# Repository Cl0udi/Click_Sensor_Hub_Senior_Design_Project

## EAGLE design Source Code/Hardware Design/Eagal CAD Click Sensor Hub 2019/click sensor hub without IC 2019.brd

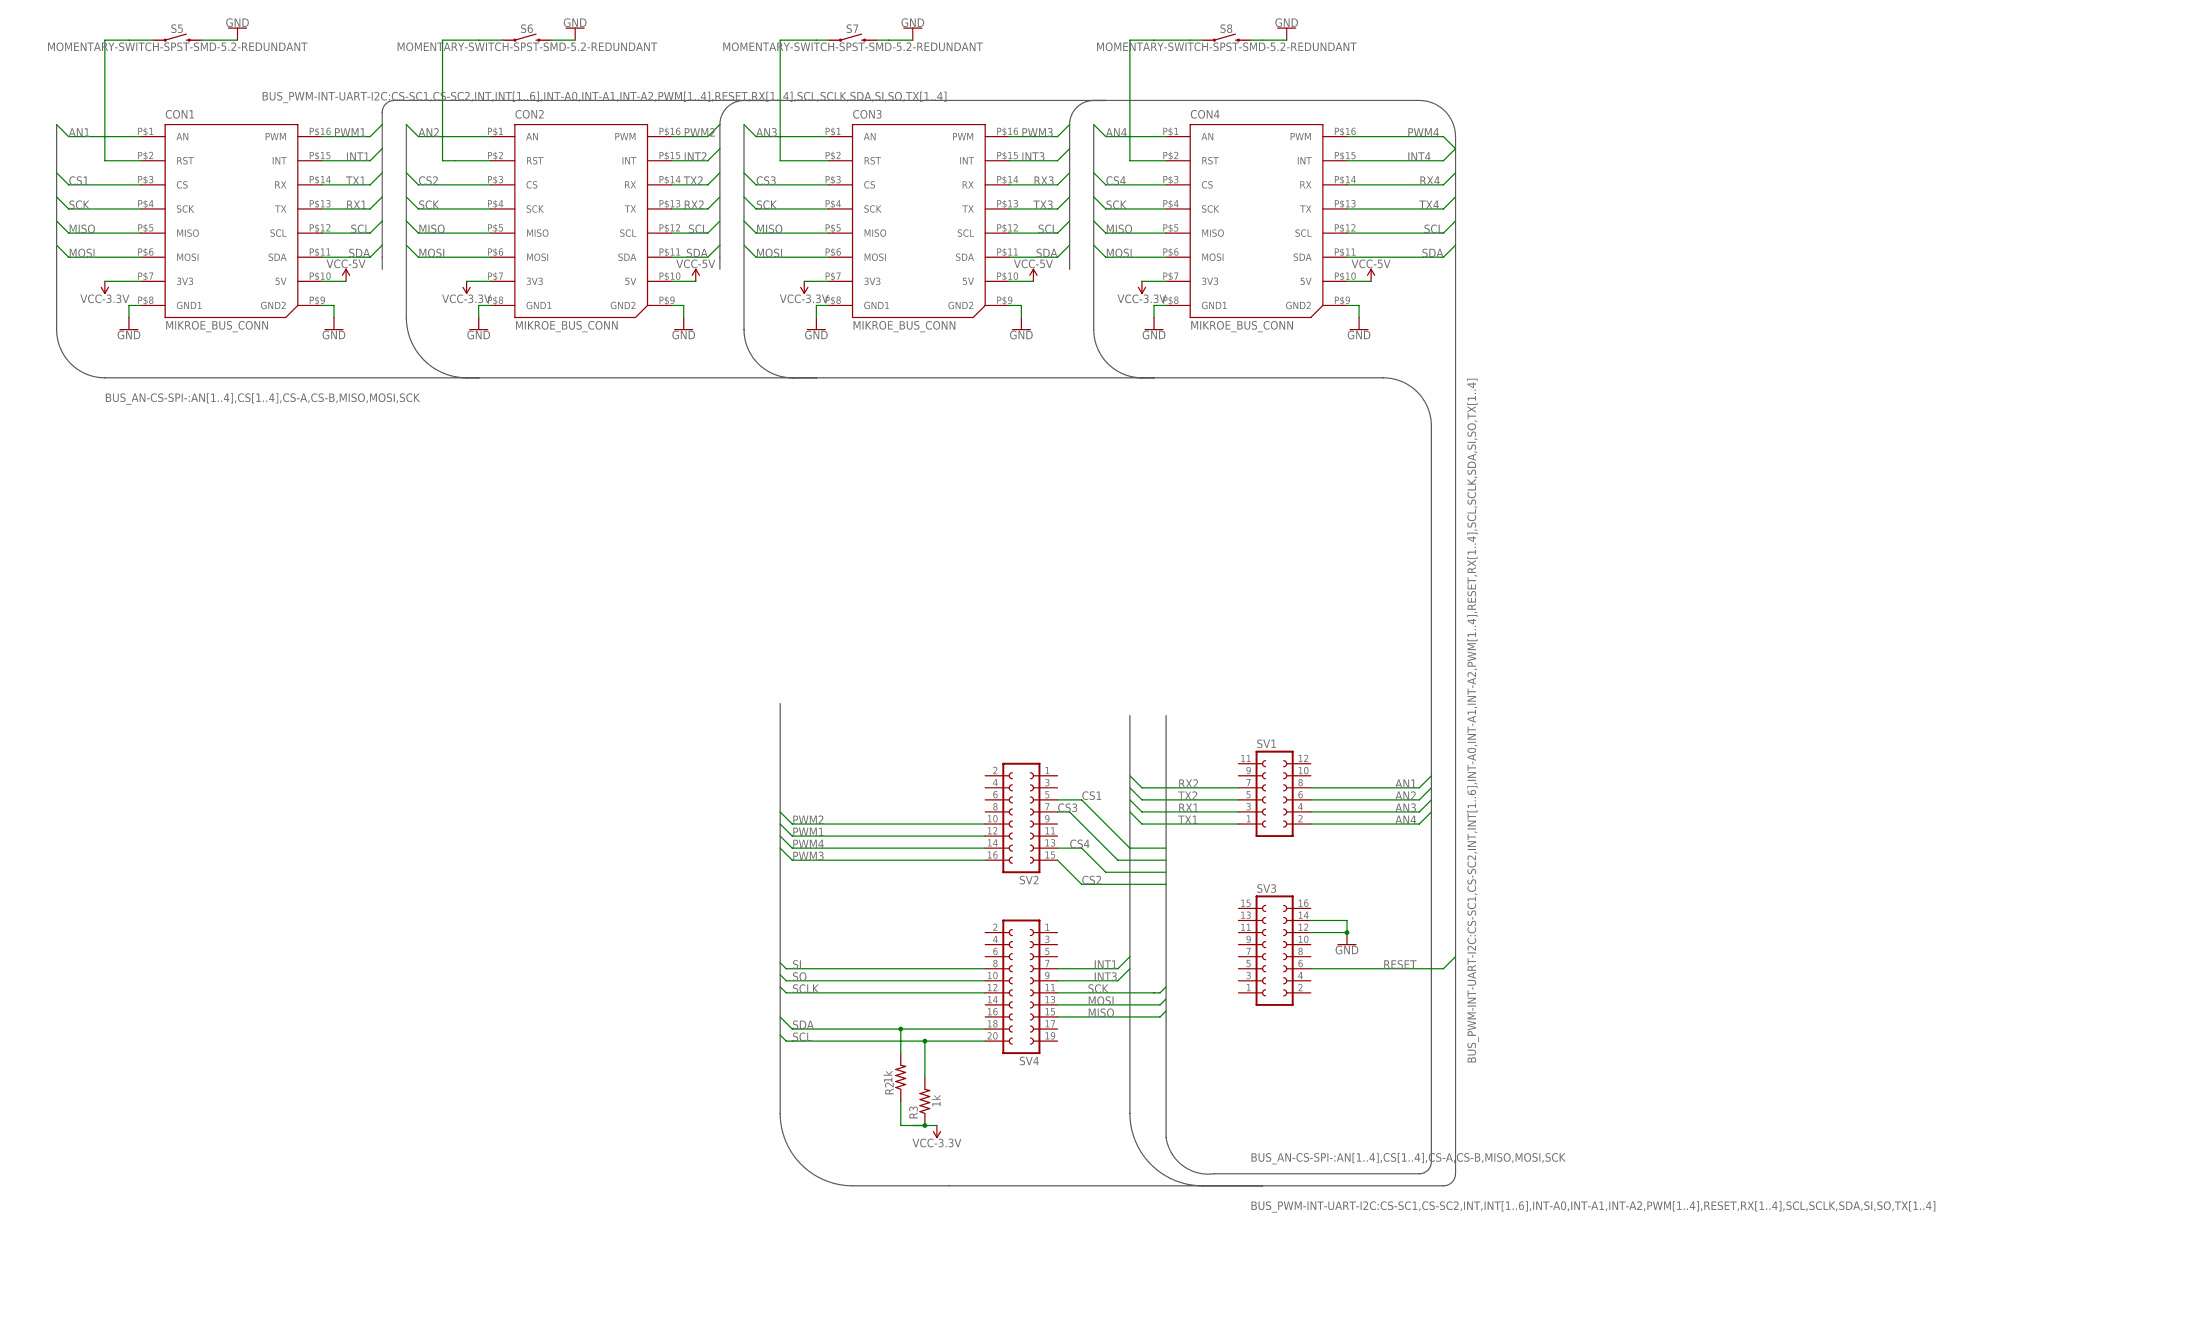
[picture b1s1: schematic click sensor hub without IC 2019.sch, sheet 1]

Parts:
CON1, CON2, CON3, CON4: MIKROE_BUS_CONN; MIKROBUS_HOST_CONN
R2, R3: 1k; R0805
S5, S6, S7, S8: MOMENTARY-SWITCH-SPST-SMD-5.2-REDUNDANT; TACTILE_SWITCH_SMD_5.2MM
SV1: FE06-2
SV2, SV3: FE08-2
SV4: FE10-2

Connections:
3.3V: CON1.P$7 (3V3), CON2.P$7 (3V3), CON3.P$7 (3V3), CON4.P$7 (3V3); also elsewhere on the board
5V: CON1.P$10 (5V), CON2.P$10 (5V), CON3.P$10 (5V), CON4.P$10 (5V); also elsewhere on the board
AN1: CON1.P$1 (AN), SV1.8
AN2: CON2.P$1 (AN), SV1.6
AN3: CON3.P$1 (AN), SV1.4
AN4: CON4.P$1 (AN), SV1.2
CS1: CON1.P$3 (CS), SV2.5
CS2: CON2.P$3 (CS), SV2.15
CS3: CON3.P$3 (CS), SV2.7
CS4: CON4.P$3 (CS), SV2.13
GND: CON1.P$8 (GND1), CON1.P$9 (GND2), CON2.P$8 (GND1), CON2.P$9 (GND2), CON3.P$8 (GND1), CON3.P$9 (GND2), CON4.P$8 (GND1), CON4.P$9 (GND2), S5.3 (2), S5.4 (2), S6.3 (2), S6.4 (2), S7.3 (2), S7.4 (2), S8.3 (2), S8.4 (2), SV3.12, SV3.14; also elsewhere on the board
INT1: CON1.P$15 (INT), SV4.7
INT2: CON2.P$15 (INT)
INT3: CON3.P$15 (INT), SV4.9
INT4: CON4.P$15 (INT)
MISO: CON1.P$5 (MISO), CON2.P$5 (MISO), CON3.P$5 (MISO), CON4.P$5 (MISO), SV4.15
MOSI: CON1.P$6 (MOSI), CON2.P$6 (MOSI), CON3.P$6 (MOSI), CON4.P$6 (MOSI), SV4.13
unnamed: CON4.P$2 (RST), S8.1, S8.2 (1)
unnamed: CON1.P$2 (RST), S5.1, S5.2 (1)
unnamed: CON2.P$2 (RST), S6.1, S6.2 (1)
unnamed: CON3.P$2 (RST), S7.1, S7.2 (1)
PWM1: CON1.P$16 (PWM), SV2.12
PWM2: CON2.P$16 (PWM), SV2.10
PWM3: CON3.P$16 (PWM), SV2.16
PWM4: CON4.P$16 (PWM), SV2.14
RESET: SV3.6
RX1: CON1.P$13 (TX), SV1.3
RX2: CON2.P$13 (TX), SV1.7
RX3: CON3.P$14 (RX)
RX4: CON4.P$14 (RX)
SCK: CON1.P$4 (SCK), CON2.P$4 (SCK), CON3.P$4 (SCK), CON4.P$4 (SCK), SV4.11
SCL: CON1.P$12 (SCL), CON2.P$12 (SCL), CON3.P$12 (SCL), CON4.P$12 (SCL), R3.2, SV4.20
SCLK: SV4.12
SDA: CON1.P$11 (SDA), CON2.P$11 (SDA), CON3.P$11 (SDA), CON4.P$11 (SDA), R2.2, SV4.18
SI: SV4.8
SO: SV4.10
TX1: CON1.P$14 (RX), SV1.1
TX2: CON2.P$14 (RX), SV1.5
TX3: CON3.P$13 (TX)
TX4: CON4.P$13 (TX)
VDD: R2.1, R3.1

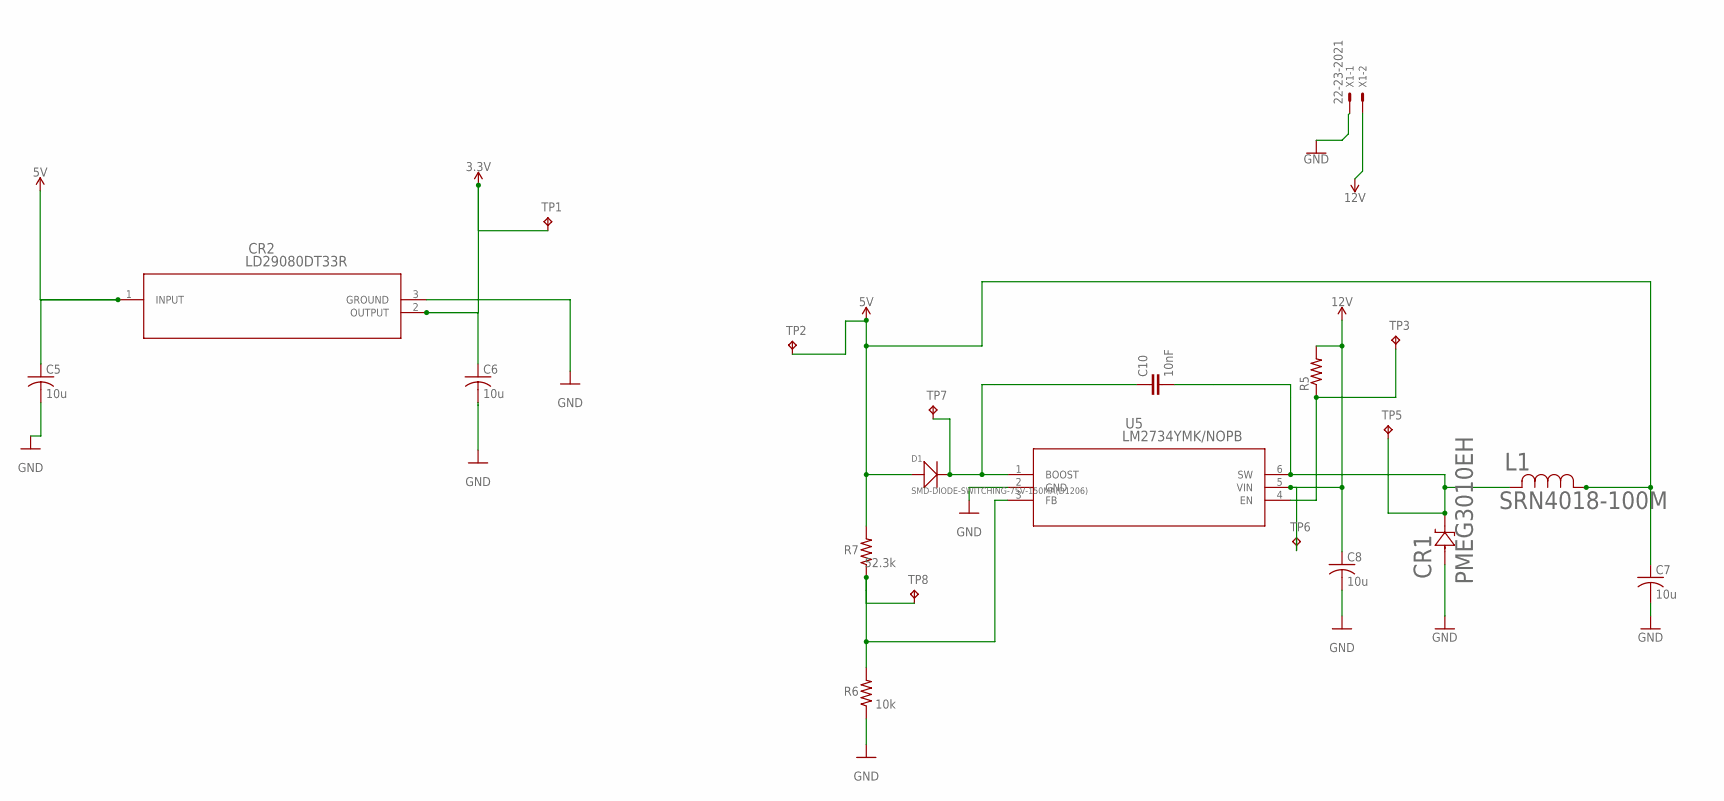
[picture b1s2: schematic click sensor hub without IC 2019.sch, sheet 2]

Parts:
C5, C6, C7, C8: 10u; C0603K
C10: 10nF; 0603
CR1: PMEG3010EH; SOD123F
CR2: LD29080DT33R; DPAK
D1: SMD-DIODE-SWITCHING-75V-150MA(D1206); LED-1206
L1: SRN4018-100M; IND_BOURNS_SRN4018
R5: R-US_R0603; R0603
R6: 10k; R0603
R7: 52.3k; R0603
TP1, TP2: TPTP20SQ; TP20SQ
TP3: TPTP14SQ; TP14SQ
TP5: TPTP07SQ; TP07SQ
TP6: TPTP15SQ; TP15SQ
TP7: TPTP08SQ; TP08SQ
TP8: TPTP09SQ; TP09SQ
U5: LM2734YMK/NOPB; MK06A
X1: 22-23-2021

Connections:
3.3V: C6.1, CR2.2 (OUTPUT), TP1.TP; also elsewhere on the board
5V: C5.1, C7.1, CR2.1 (INPUT), D1.+, L1.1, R7.2, TP2.TP; also elsewhere on the board
12V: C8.1, R5.2, TP6.TP, U5.5 (VIN), X1.2
GND: C5.2, C6.2, C7.2, C8.2, CR1.2 (22), CR2.3 (GROUND), R6.1, U5.2 (GND), X1.1; also elsewhere on the board
unnamed: R5.1, TP3.TP, U5.4 (EN)
unnamed: C10.1, D1.-, TP7.TP, U5.1 (BOOST)
unnamed: R6.2, R7.1, TP8.TP, U5.3 (FB)
unnamed: C10.2, CR1.1 (11), L1.2, TP5.TP, U5.6 (SW)

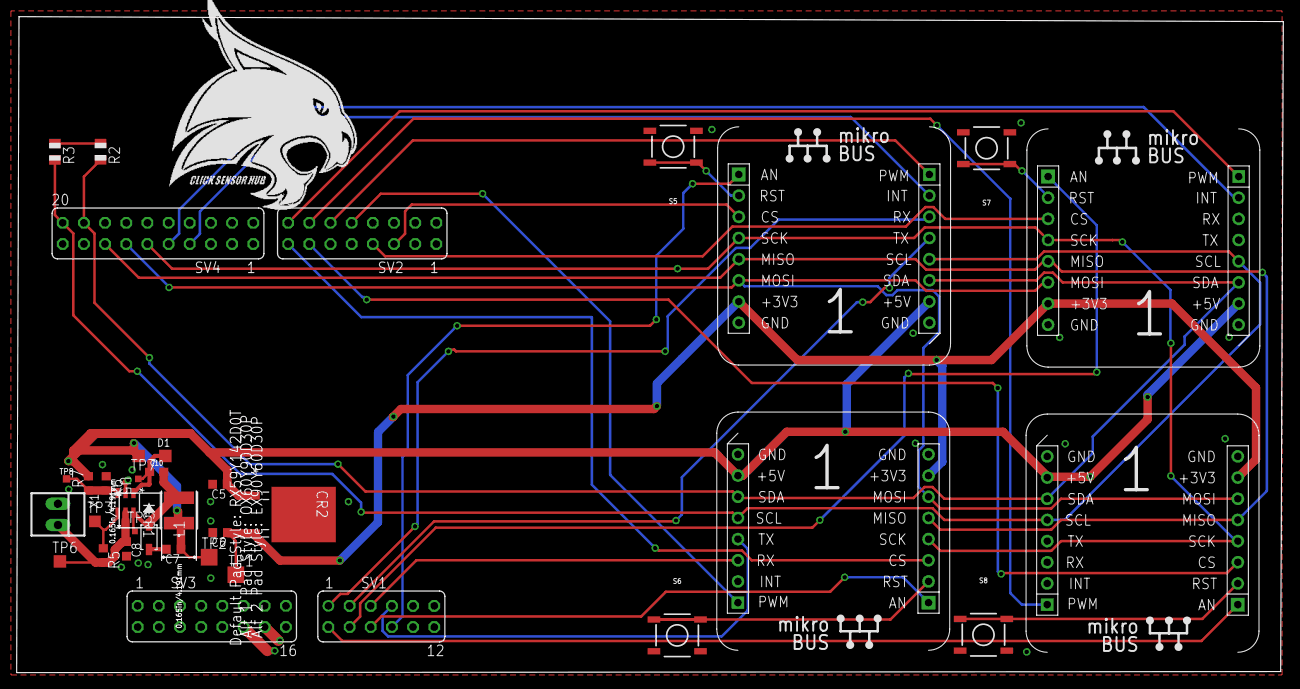
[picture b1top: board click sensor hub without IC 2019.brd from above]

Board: 2 copper layers, 151.8 x 78.5 mm, 35 parts (0 on the bottom side), 36 nets.

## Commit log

2019-05-13 Initial Commit
    All files uploaded from Senior Design Sharepoint, still need to upload Hardware design files once I recieve them from Mo
2019-05-13 Added Hardware Files
    All eagle CAD files uploaded
2019-12-26 Final Commits
    Last minute spelling and spacing
2020-03-08 `vallen` is verified to be less than `len`, therefore, it can never be the case that `vallen >= len + sizeof(rhostname)`.
    This PR fixes the check so the `rhostname` array does not overflow.
    Reported-by: Github Security Lab <securitylab@github.com>

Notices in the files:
parts and their libraries:
SparkFun-Capacitors: Licensing: Creative Commons ShareAlike 4.0 International - https://creativecommons.org/licenses/by-sa/4.0
